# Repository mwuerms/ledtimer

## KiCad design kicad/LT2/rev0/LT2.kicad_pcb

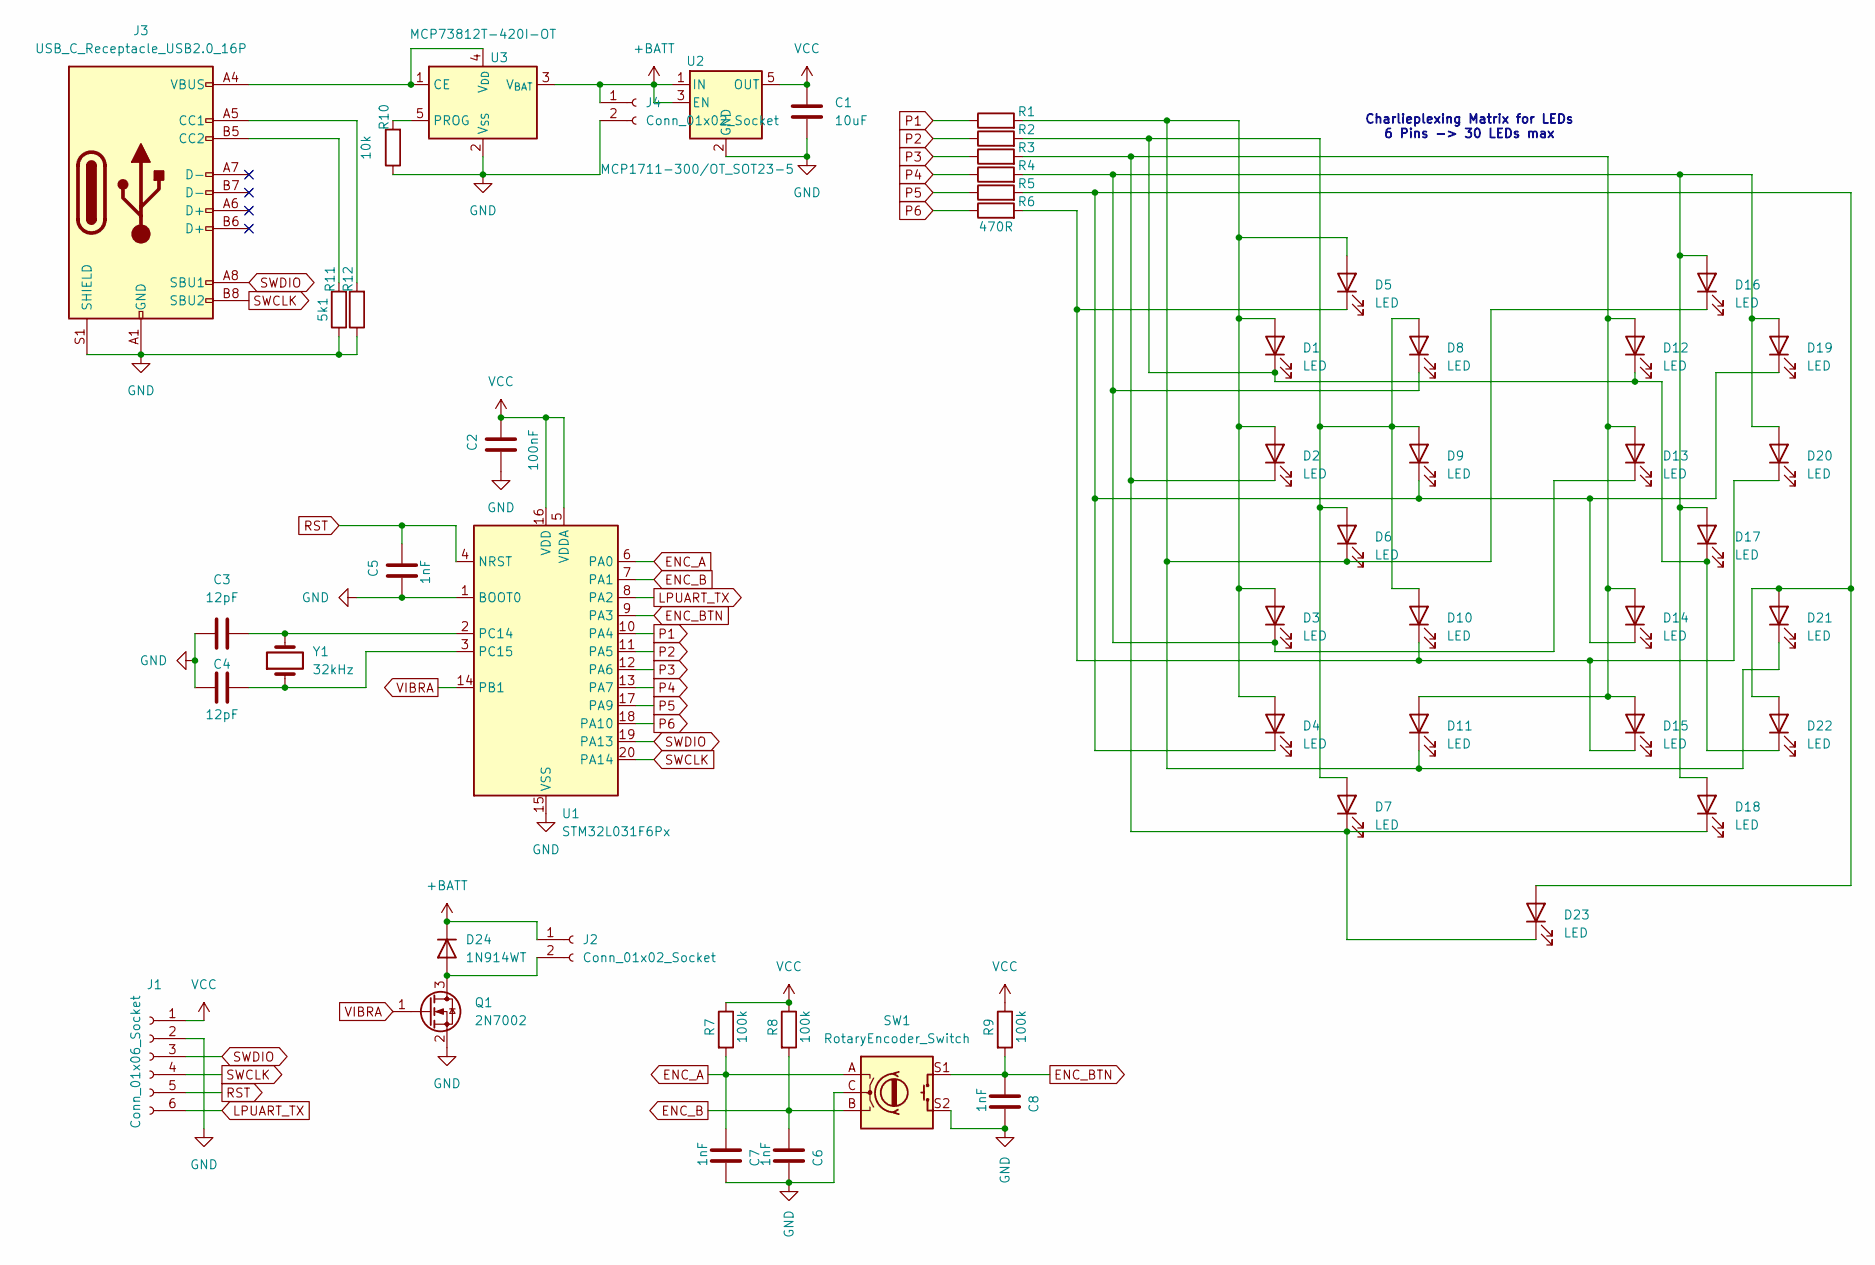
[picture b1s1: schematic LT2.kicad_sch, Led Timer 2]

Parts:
C1: 10uF; C_0805_2012Metric
C2: 100nF; C_0603_1608Metric
C3, C4: 12pF; C_0603_1608Metric
C5, C6, C7, C8: 1nF; C_0603_1608Metric
D1, D2, D3, D4, D5, D6, D7, D8, D9, D10, D11, D12, D13, D14, D15, D16, D17, D18, D19, D20, D21, D22, D23: LED; LED_0603_1608Metric_Pad1.05x0.95mm_HandSolder
D24: 1N914WT; D_SOD-523
J1: Conn_01x06_Socket; PinHeader_1x06_P1.27mm_Vertical
J2, J4: Conn_01x02_Socket; PinHeader_1x02_P1.27mm_Vertical
J3: USB_C_Receptacle_USB2.0_16P; USB_C_Receptacle_G-Switch_GT-USB-7010ASV
Q1: 2N7002; SOT-23
R1, R2, R3, R4, R5, R6: 470R; R_0603_1608Metric
R7, R8, R9: 100k; R_0603_1608Metric
R10: 10k; R_0603_1608Metric
R11, R12: 5k1; R_0603_1608Metric
SW1: RotaryEncoder_Switch; rotary_encoder_PEC11S-929K
U1: STM32L031F6Px; TSSOP-20_4.4x6.5mm_P0.65mm
U2: MCP1711-300/OT_SOT23-5; SOT-23-5
U3: MCP73812T-420I-OT; SOT-23-5
Y1: 32kHz; Crystal_SMD_3215-2Pin_3.2x1.5mm

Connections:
+BATT: D24.1 (K), J2.1, J4.1, U2.1 (IN), U2.3 (EN), U3.3 (V_{BAT})
ENC_A: C7.2, R7.2, SW1.A, U1.6 (PA0)
ENC_B: C6.2, R8.2, SW1.B, U1.7 (PA1)
ENC_BTN: C8.2, R9.2, SW1.S1, U1.9 (PA3)
GND: C1.2, C2.2, C3.1, C4.1, C5.2, C6.1, C7.1, C8.1, J1.2, J3.A1 (GND), J3.A12 (GND), J3.B1 (GND), J3.B12 (GND), J3.S1 (SHIELD), J4.2, Q1.2 (S), R10.1, R11.1, R12.1, SW1.C, SW1.S2, U1.1 (BOOT0), U1.15 (VSS), U2.2 (GND), U3.2 (V_{SS})
LPUART_TX: J1.6, U1.8 (PA2)
unnamed: D1.2 (A), D2.2 (A), D3.2 (A), D4.2 (A), D5.2 (A), D6.1 (K), D11.1 (K), D16.1 (K), D21.1 (K), R1.2
unnamed: D1.1 (K), D6.2 (A), D7.2 (A), D8.2 (A), D9.2 (A), D10.2 (A), D12.1 (K), D17.1 (K), D22.1 (K), R2.2
unnamed: D5.1 (K), D10.1 (K), D15.1 (K), D20.1 (K), R6.2
unnamed: D2.1 (K), D7.1 (K), D11.2 (A), D12.2 (A), D13.2 (A), D14.2 (A), D15.2 (A), D18.1 (K), D23.1 (K), R3.2
unnamed: D3.1 (K), D8.1 (K), D13.1 (K), D16.2 (A), D17.2 (A), D18.2 (A), D19.2 (A), D20.2 (A), R4.2
unnamed: D4.1 (K), D9.1 (K), D14.1 (K), D19.1 (K), D21.2 (A), D22.2 (A), D23.2 (A), R5.2
unnamed: D24.2 (A), J2.2, Q1.3 (D)
unnamed: J3.A5 (CC1), R12.2
unnamed: J3.B5 (CC2), R11.2
unnamed: C3.2, U1.2 (PC14), Y1.2
unnamed: C4.2, U1.3 (PC15), Y1.1
unnamed: J3.A4 (VBUS), J3.A9 (VBUS), J3.B4 (VBUS), J3.B9 (VBUS), U3.1 (CE), U3.4 (V_{DD})
unnamed: R10.2, U3.5 (PROG)
P1: R1.1, U1.10 (PA4)
P2: R2.1, U1.11 (PA5)
P3: R3.1, U1.12 (PA6)
P4: R4.1, U1.13 (PA7)
P5: R5.1, U1.17 (PA9)
P6: R6.1, U1.18 (PA10)
RST: C5.1, J1.5, U1.4 (NRST)
SWCLK: J1.4, J3.B8 (SBU2), U1.20 (PA14)
SWDIO: J1.3, J3.A8 (SBU1), U1.19 (PA13)
VCC: C1.1, C2.1, J1.1, R7.1, R8.1, R9.1, U1.5 (VDDA), U1.16 (VDD), U2.5 (OUT)
VIBRA: Q1.1 (G), U1.14 (PB1)

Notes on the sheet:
Charlieplexing Matrix for LEDs 6 Pins -> 30 LEDs max

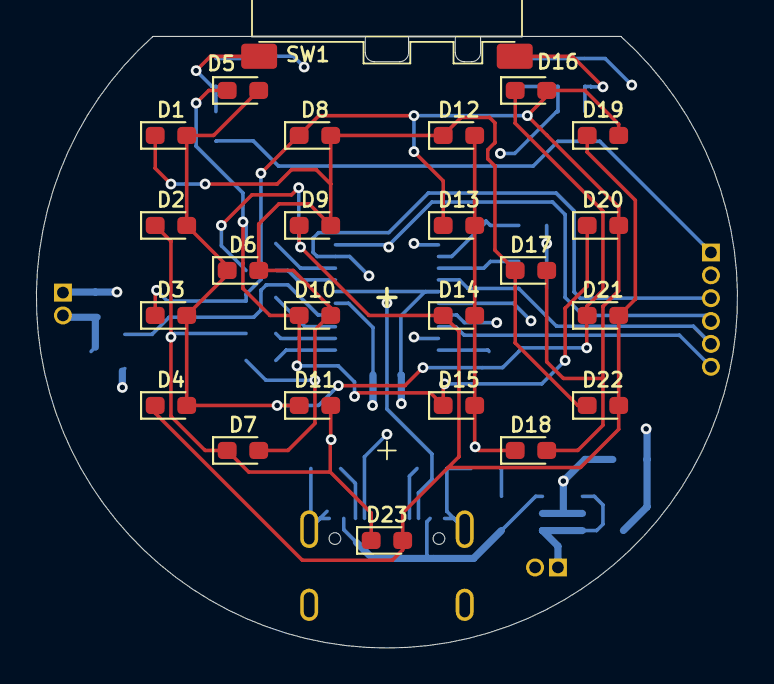
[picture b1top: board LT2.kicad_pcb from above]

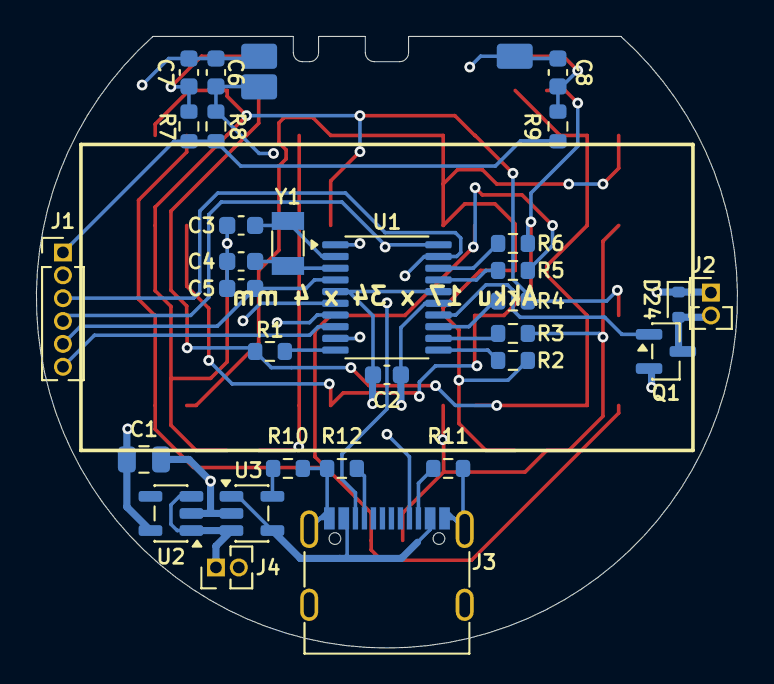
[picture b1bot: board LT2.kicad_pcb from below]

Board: 4 copper layers, 38.9 x 34.0 mm, 54 parts (30 on the bottom side), 30 nets.

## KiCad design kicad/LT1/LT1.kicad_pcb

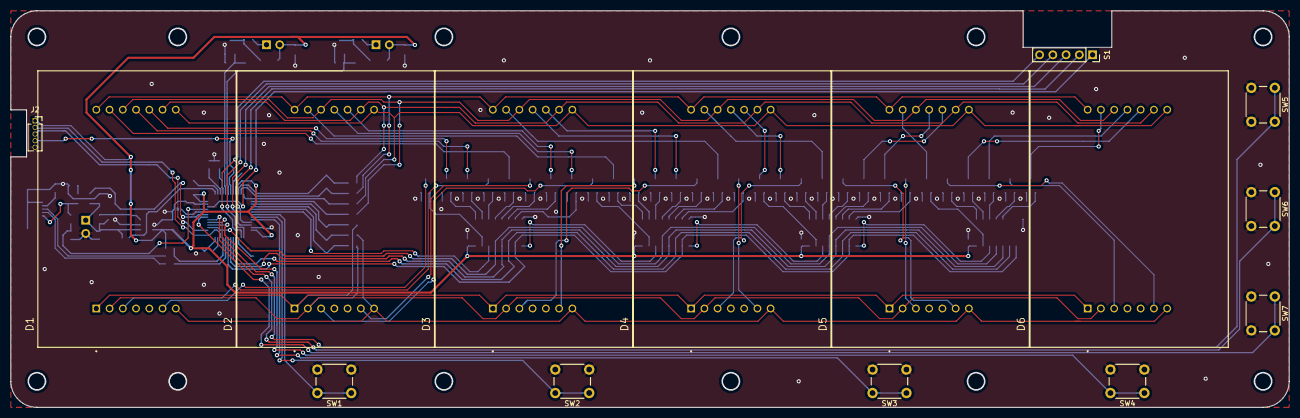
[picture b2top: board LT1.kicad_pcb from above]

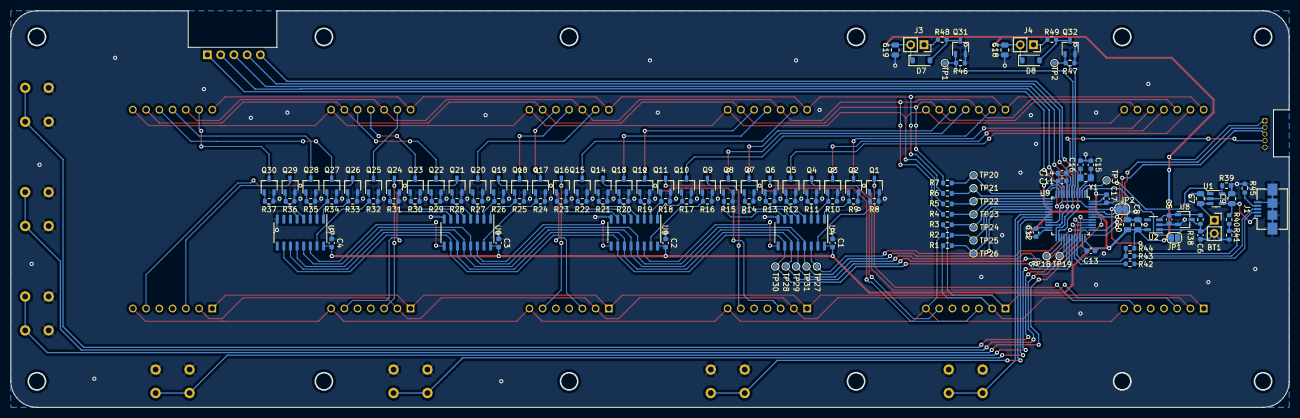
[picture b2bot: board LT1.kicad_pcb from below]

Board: 2 copper layers, 245.0 x 76.0 mm, 149 parts (134 on the bottom side), 123 nets.

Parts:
BT1: Battery_Cell; PinSocket_1x02_P2.54mm_Vertical
C1, C2, C3, C4, C6, C11, C12, C13, C17: 100nF; C_0603_1608Metric
C5, C14: 10nF; C_0603_1608Metric
C7, C8, C9, C10, C18, C19: 10uF; C_0805_2012Metric
C15, C16: C_0603_1608Metric
D1, D2, D3, D4, D5, D6: TC20-11SRWA; LED_TC20-11SRWA
D7, D8: D_Schottky; D_SOD-123
J1: USB_B_Micro; USB_Micro-B_Amphenol_10104110_Horizontal
J2: Conn_01x05_Socket; PinSocket_1x05_P1.27mm_Vertical
J3, J4: Conn_01x02_Socket; PinSocket_1x02_P2.54mm_Vertical
JP1: SolderJumper_2_Open; SolderJumper-2_P1.3mm_Open_RoundedPad1.0x1.5mm
JP2: SolderJumper_2_Bridged; SolderJumper-2_P1.3mm_Bridged_RoundedPad1.0x1.5mm
Q1, Q2, Q3, Q4, Q5, Q6, Q7, Q8, Q9, Q10, Q11, Q12, Q13, Q14, Q15, Q16, Q17, Q18, Q19, Q20, Q21, Q22, Q23, Q24, Q25, Q26, Q27, Q28, Q29, Q30, Q31, Q32: 2N7002K; TSOT-23
R1, R2, R3, R4, R5, R6, R7: 150R; R_0603_1608Metric
R8, R9, R10, R11, R12, R13, R14, R15, R16, R17, R18, R19, R20, R21, R22, R23, R24, R25, R26, R27, R28, R29, R30, R31, R32, R33, R34, R35, R36, R37, R38, R39, R46, R47, R48, R49: 1M; R_0603_1608Metric
R40, R41, R45: 10k; R_0603_1608Metric
R42, R43: 10R; R_0603_1608Metric
R44: 1k5; R_0603_1608Metric
S1: MF140; PinSocket_1x05_P2.54mm_Vertical
SW1, SW2, SW3, SW4, SW5, SW6, SW7: SW_Push; SW_PUSH_6mm_H9.5mm
TP1, TP2, TP3, TP18, TP19, TP20, TP21, TP22, TP23, TP24, TP25, TP26, TP27, TP28, TP29, TP30, TP31: TestPoint; TestPoint_Pad_D1.0mm
U1: MCP73831-2-OT; SOT-23-5
U2: TLV75533PDBV; SOT-23-5
U4, U5, U6, U7: 74HC595D; SO-16_3.9x9.9mm_P1.27mm
U8: MCP111T-xxxE_TT; TSOT-23
U9: STM32L412C8Tx; LQFP-48_7x7mm_P0.5mm
Y1: 32 kHz (ABS06); R_0805_2012Metric_Pad1.20x1.40mm_HandSolder

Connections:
+3.3V: C1.1, C2.1, C3.1, C4.1, C8.1, C10.1, C11.1, C12.1, C13.1, C17.1, C18.1, C19.1, D7.1 (K), D8.1 (K), J2.1, J3.2, J4.2, R44.2, U2.5 (OUT), U4.16 (VCC), U5.16 (VCC), U6.16 (VCC), U7.16 (VCC), U9.9 (VDDA), U9.24 (VDD), U9.36 (VDDUSB), U9.48 (VDD)
+BATT: BT1.1 (+), C6.1, C7.1, JP1.1 (A), R38.1, U1.3 (V_{BAT}), U2.1 (IN), U8.3 (VDD)
ALM0: Q31.1 (G), R46.1, TP1.1, U9.6 (PH1)
ALM1: Q32.1 (G), R47.1, TP2.1, U9.5 (PH0)
BTN_MODE: SW6.1, U9.41 (PB5)
BTN_PLAY: SW5.1, U9.40 (PB4)
BTN_STOP: SW7.1, U9.42 (PB6)
BTN_UP1: SW1.1, U9.18 (PB0)
BTN_UP2: SW2.1, U9.19 (PB1)
BTN_UP3: SW3.1, U9.20 (PB2)
BTN_UP4: SW4.1, U9.39 (PB3)
CH_STAT: U1.1 (STAT), U9.43 (PB7)
DISP_COL_OE: TP31.1, U4.13 (~OE), U5.13 (~OE), U6.13 (~OE), U7.13 (~OE), U9.38 (PA15)
DISP_COL_RCLK: TP29.1, U4.12 (RCLK), U5.12 (RCLK), U6.12 (RCLK), U7.12 (RCLK), U9.30 (PA9)
DISP_COL_SER: TP27.1, U4.14 (SER), U9.17 (PA7)
DISP_COL_SRCLK: TP28.1, U4.11 (SRCLK), U5.11 (SRCLK), U6.11 (SRCLK), U7.11 (SRCLK), U9.29 (PA8)
DISP_COL_SRCLR: TP30.1, U4.10 (~SRCLR), U5.10 (~SRCLR), U6.10 (~SRCLR), U7.10 (~SRCLR), U9.31 (PA10)
DISP_ROW0: R7.1, TP20.1, U9.10 (PA0)
DISP_ROW1: R6.1, TP21.1, U9.11 (PA1)
DISP_ROW2: R5.1, TP22.1, U9.12 (PA2)
DISP_ROW3: R4.1, TP23.1, U9.13 (PA3)
DISP_ROW4: R3.1, TP24.1, U9.14 (PA4)
DISP_ROW5: R2.1, TP25.1, U9.15 (PA5)
DISP_ROW6: R1.1, TP26.1, U9.16 (PA6)
GND: BT1.2 (-), C1.2, C2.2, C3.2, C4.2, C5.2, C6.2, C7.2, C8.2, C9.2, C10.2, C11.2, C12.2, C13.2, C14.2, C15.1, C16.1, C17.2, C18.2, C19.2, J1.5 (GND), J1.6 (Shield), J2.5, JP2.1 (A), Q1.2 (S), Q2.2 (S), Q3.2 (S), Q4.2 (S), Q5.2 (S), Q6.2 (S), Q7.2 (S), Q8.2 (S), Q9.2 (S), Q10.2 (S), Q11.2 (S), Q12.2 (S), Q13.2 (S), Q14.2 (S), Q15.2 (S), Q16.2 (S), Q17.2 (S), Q18.2 (S), Q19.2 (S), Q20.2 (S), Q21.2 (S), Q22.2 (S), Q23.2 (S), Q24.2 (S), Q25.2 (S), Q26.2 (S), Q27.2 (S), Q28.2 (S), Q29.2 (S), Q30.2 (S), Q31.2 (S), Q32.2 (S), R8.2, R9.2, R10.2, R11.2, R12.2, R13.2, R14.2, R15.2, R16.2, R17.2, R18.2, R19.2, R20.2, R21.2, R22.2, R23.2, R24.2, R25.2, R26.2, R27.2, R28.2, R29.2, R30.2, R31.2, R32.2, R33.2, R34.2, R35.2, R36.2, R37.2, R39.2, R41.2, R45.2, R46.2, R47.2, SW1.2, SW2.2, SW3.2, SW4.2, SW5.2, SW6.2, SW7.2, U1.2 (V_{SS}), U2.2 (GND), U4.8 (GND), U5.8 (GND), U6.8 (GND), U7.8 (GND), U8.2 (VSS), U9.8 (VSSA), U9.23 (VSS), U9.35 (VSS), U9.47 (VSS)
unnamed: D1.13 (C1), Q5.3 (D)
unnamed: D1.3 (C2), Q4.3 (D)
unnamed: D1.11 (C3), Q3.3 (D)
unnamed: D1.10 (C4), Q2.3 (D)
unnamed: D1.6 (C5), Q1.3 (D)
unnamed: D1.9 (R1), D2.9 (R1), D3.9 (R1), D4.9 (R1), D5.9 (R1), D6.9 (R1), R7.2
unnamed: D1.14 (R2), D2.14 (R2), D3.14 (R2), D4.14 (R2), D5.14 (R2), D6.14 (R2), R6.2
unnamed: D1.8 (R3), D2.8 (R3), D3.8 (R3), D4.8 (R3), D5.8 (R3), D6.8 (R3), R5.2
unnamed: D1.12 (R4), D2.12 (R4), D3.12 (R4), D4.12 (R4), D5.12 (R4), D6.12 (R4), R4.2
unnamed: D1.1 (R5), D2.1 (R5), D3.1 (R5), D4.1 (R5), D5.1 (R5), D6.1 (R5), R3.2
unnamed: D1.7 (R6), D2.7 (R6), D3.7 (R6), D4.7 (R6), D5.7 (R6), D6.7 (R6), R2.2
unnamed: D1.2 (R7), D2.2 (R7), D3.2 (R7), D4.2 (R7), D5.2 (R7), D6.2 (R7), R1.2
unnamed: D2.13 (C1), Q10.3 (D)
unnamed: D2.3 (C2), Q9.3 (D)
unnamed: D2.11 (C3), Q8.3 (D)
unnamed: D2.10 (C4), Q7.3 (D)
unnamed: D2.6 (C5), Q6.3 (D)
unnamed: D3.13 (C1), Q15.3 (D)
unnamed: D3.3 (C2), Q14.3 (D)
unnamed: D3.11 (C3), Q13.3 (D)
unnamed: D3.10 (C4), Q12.3 (D)
unnamed: D3.6 (C5), Q11.3 (D)
unnamed: D4.13 (C1), Q20.3 (D)
unnamed: D4.3 (C2), Q19.3 (D)
unnamed: D4.11 (C3), Q18.3 (D)
unnamed: D4.10 (C4), Q17.3 (D)
unnamed: D4.6 (C5), Q16.3 (D)
unnamed: D5.13 (C1), Q25.3 (D)
unnamed: D5.3 (C2), Q24.3 (D)
unnamed: D5.11 (C3), Q23.3 (D)
unnamed: D5.10 (C4), Q22.3 (D)
unnamed: D5.6 (C5), Q21.3 (D)
unnamed: D6.13 (C1), Q30.3 (D)
unnamed: D6.3 (C2), Q29.3 (D)
unnamed: D6.11 (C3), Q28.3 (D)
unnamed: D6.10 (C4), Q27.3 (D)
unnamed: D6.6 (C5), Q26.3 (D)
unnamed: D7.2 (A), Q31.3 (D), R48.2
unnamed: D8.2 (A), Q32.3 (D), R49.2
unnamed: J1.4 (ID), R45.1
unnamed: J3.1, R48.1
unnamed: J4.1, R49.1
unnamed: JP1.2 (B), U9.1 (VBAT)
unnamed: JP2.2 (B), U9.44 (PH3)
unnamed: Q1.1 (G), R8.1, U4.15 (QA)
unnamed: Q2.1 (G), R9.1, U4.1 (QB)
unnamed: Q3.1 (G), R10.1, U4.2 (QC)
unnamed: Q4.1 (G), R11.1, U4.3 (QD)
unnamed: Q5.1 (G), R12.1, U4.4 (QE)
unnamed: Q6.1 (G), R13.1, U4.5 (QF)
unnamed: Q7.1 (G), R14.1, U4.6 (QG)
unnamed: Q8.1 (G), R15.1, U4.7 (QH)
unnamed: Q9.1 (G), R16.1, U5.15 (QA)
unnamed: Q10.1 (G), R17.1, U5.1 (QB)
unnamed: Q11.1 (G), R18.1, U5.2 (QC)
unnamed: Q12.1 (G), R19.1, U5.3 (QD)
unnamed: Q13.1 (G), R20.1, U5.4 (QE)
unnamed: Q14.1 (G), R21.1, U5.5 (QF)
unnamed: Q15.1 (G), R22.1, U5.6 (QG)
unnamed: Q16.1 (G), R23.1, U5.7 (QH)
unnamed: Q17.1 (G), R24.1, U6.15 (QA)
unnamed: Q18.1 (G), R25.1, U6.1 (QB)
unnamed: Q19.1 (G), R26.1, U6.2 (QC)
unnamed: Q20.1 (G), R27.1, U6.3 (QD)
unnamed: Q21.1 (G), R28.1, U6.4 (QE)
unnamed: Q22.1 (G), R29.1, U6.5 (QF)
unnamed: Q23.1 (G), R30.1, U6.6 (QG)
unnamed: Q24.1 (G), R31.1, U6.7 (QH)
unnamed: Q25.1 (G), R32.1, U7.15 (QA)
unnamed: Q26.1 (G), R33.1, U7.1 (QB)
unnamed: Q27.1 (G), R34.1, U7.2 (QC)
unnamed: Q28.1 (G), R35.1, U7.3 (QD)
unnamed: Q29.1 (G), R36.1, U7.4 (QE)
unnamed: Q30.1 (G), R37.1, U7.5 (QF)
unnamed: R39.1, U1.5 (PROG)
unnamed: C5.1, R38.2, U2.3 (EN), U8.1 (VOUT)
unnamed: U4.9 (QH'), U5.14 (SER)
unnamed: U5.9 (QH'), U6.14 (SER)
unnamed: U6.9 (QH'), U7.14 (SER)
unnamed: R42.1, U9.32 (PA11)
unnamed: R43.1, R44.1, U9.33 (PA12)
unnamed: TP18.1, U9.27 (PB14)
unnamed: TP19.1, U9.28 (PB15)
unnamed: TP3.1, U9.2 (PC13)
unnamed: C15.2, U9.3 (PC14), Y1.2
unnamed: C16.2, U9.4 (PC15), Y1.1
SW0: S1.1, U9.46 (PB9)
SW1: S1.2, U9.21 (PB10)
SW2: S1.3, U9.22 (PB11)
SW3: S1.4, U9.25 (PB12)
SW4: S1.5, U9.26 (PB13)
SWDCLK: J2.3, U9.37 (PA14)
SWDIO: J2.2, U9.34 (PA13)
USBD+: J1.3 (D+), R43.2
USBD-: J1.2 (D-), R42.2
USB_STAT: R40.2, R41.1, U9.45 (PB8)
VBUS: C9.1, J1.1 (VBUS), R40.1, U1.4 (V_{DD})
nRST: C14.1, J2.4, U9.7 (NRST)

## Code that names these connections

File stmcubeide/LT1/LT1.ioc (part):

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Mcu.Name=STM32L412CBTx
Mcu.Package=LQFP48
Mcu.UserName=STM32L412CBTx
PA0.GPIOParameters=GPIO_Speed,GPIO_Label
PA0.GPIO_Label=DISP_ROW0
PA0.GPIO_Speed=GPIO_SPEED_FREQ_HIGH
PA0.Signal=GPIO_Output
PA1.GPIOParameters=GPIO_Speed,GPIO_Label
PA1.GPIO_Label=DISP_ROW1
PA1.GPIO_Speed=GPIO_SPEED_FREQ_HIGH
PA1.Signal=GPIO_Output
PA10.GPIOParameters=GPIO_Speed,GPIO_Label
PA10.GPIO_Label=DISP_COL_SRCLR
PA10.GPIO_Speed=GPIO_SPEED_FREQ_HIGH
PA10.Signal=GPIO_Output
PA13\ (JTMS/SWDIO).Mode=Serial_Wire
PA13\ (JTMS/SWDIO).Signal=SYS_JTMS-SWDIO
PA14\ (JTCK/SWCLK).Mode=Serial_Wire
PA14\ (JTCK/SWCLK).Signal=SYS_JTCK-SWCLK
PA15\ (JTDI).GPIOParameters=GPIO_Speed,GPIO_Label
PA15\ (JTDI).GPIO_Label=DISP_COL_OE
PA15\ (JTDI).GPIO_Speed=GPIO_SPEED_FREQ_HIGH
PA15\ (JTDI).Signal=GPIO_Output
PA2.GPIOParameters=GPIO_Speed,GPIO_Label
PA2.GPIO_Label=DISP_ROW2
PA2.GPIO_Speed=GPIO_SPEED_FREQ_HIGH
PA2.Signal=GPIO_Output
PA3.GPIOParameters=GPIO_Speed,GPIO_Label
PA3.GPIO_Label=DISP_ROW3
PA3.GPIO_Speed=GPIO_SPEED_FREQ_HIGH
PA3.Signal=GPIO_Output
PA4.GPIOParameters=GPIO_Speed,GPIO_Label
PA4.GPIO_Label=DISP_ROW4
PA4.GPIO_Speed=GPIO_SPEED_FREQ_HIGH
PA4.Signal=GPIO_Output
PA5.GPIOParameters=GPIO_Speed,GPIO_Label
PA5.GPIO_Label=DISP_ROW5
PA5.GPIO_Speed=GPIO_SPEED_FREQ_HIGH
PA5.Signal=GPIO_Output
PA6.GPIOParameters=GPIO_Speed,GPIO_Label
PA6.GPIO_Label=DISP_ROW6
PA6.GPIO_Speed=GPIO_SPEED_FREQ_HIGH
PA6.Signal=GPIO_Output
PA7.GPIOParameters=GPIO_Speed,GPIO_Label
PA7.GPIO_Label=DISP_COL_SER
PA7.GPIO_Speed=GPIO_SPEED_FREQ_HIGH
PA7.Signal=GPIO_Output
PA8.GPIOParameters=GPIO_Speed,GPIO_Label
PA8.GPIO_Label=DISP_COL_SRCLK
PA8.GPIO_Speed=GPIO_SPEED_FREQ_HIGH
PA8.Signal=GPIO_Output
PA9.GPIOParameters=GPIO_Speed,GPIO_Label
PA9.GPIO_Label=DISP_COL_RCLK
PA9.GPIO_Speed=GPIO_SPEED_FREQ_HIGH
PA9.Signal=GPIO_Output
PB0.GPIOParameters=GPIO_PuPd,GPIO_Label
PB0.GPIO_Label=BTN_UP0
PB0.GPIO_PuPd=GPIO_PULLUP
PB0.Signal=GPXTI0
PB1.GPIOParameters=GPIO_PuPd,GPIO_Label
PB1.GPIO_Label=BTN_UP1
PB1.GPIO_PuPd=GPIO_PULLUP
PB1.Signal=GPXTI1
PB10.GPIOParameters=GPIO_PuPd,GPIO_Label
PB10.GPIO_Label=SW1
PB10.GPIO_PuPd=GPIO_PULLDOWN
PB10.Signal=GPIO_Input
PB11.GPIOParameters=GPIO_PuPd,GPIO_Label
PB11.GPIO_Label=SW2
PB11.GPIO_PuPd=GPIO_PULLDOWN
PB11.Signal=GPIO_Input
PB12.GPIOParameters=GPIO_PuPd,GPIO_Label
PB12.GPIO_Label=SW3
PB12.GPIO_PuPd=GPIO_PULLDOWN
PB12.Signal=GPIO_Input
PB13.GPIOParameters=GPIO_PuPd,GPIO_Label
PB13.GPIO_Label=SW4
PB13.GPIO_PuPd=GPIO_PULLDOWN
PB13.Signal=GPIO_Input
PB2.GPIOParameters=GPIO_PuPd,GPIO_Label
PB2.GPIO_Label=BTN_UP2
PB2.GPIO_PuPd=GPIO_PULLUP
PB2.Signal=GPXTI2
PB3\ (JTDO/TRACESWO).GPIOParameters=GPIO_PuPd,GPIO_Label
PB3\ (JTDO/TRACESWO).GPIO_Label=BTN_UP3
PB3\ (JTDO/TRACESWO).GPIO_PuPd=GPIO_PULLUP
PB3\ (JTDO/TRACESWO).Signal=GPXTI3
PB4\ (NJTRST).GPIOParameters=GPIO_PuPd,GPIO_Label
PB4\ (NJTRST).GPIO_Label=BTN_PLAY
PB4\ (NJTRST).GPIO_PuPd=GPIO_PULLUP
PB4\ (NJTRST).Signal=GPXTI4
PB5.GPIOParameters=GPIO_PuPd,GPIO_Label
PB5.GPIO_Label=BTN_MODE
PB5.GPIO_PuPd=GPIO_PULLUP
PB5.Signal=GPXTI5
PB6.GPIOParameters=GPIO_PuPd,GPIO_Label
PB6.GPIO_Label=BTN_STOP
PB6.GPIO_PuPd=GPIO_PULLUP
PB6.Signal=GPXTI6
PB7.GPIOParameters=GPIO_Label
PB7.GPIO_Label=CH_STAT
PB7.Signal=GPIO_Input
PB8.GPIOParameters=GPIO_Label
PB8.GPIO_Label=USB_STAT
PB8.Signal=GPXTI8
PB9.GPIOParameters=GPIO_PuPd,GPIO_Label
PB9.GPIO_Label=SW0
PB9.GPIO_PuPd=GPIO_PULLDOWN
PB9.Signal=GPIO_Input
PC13.GPIOParameters=GPIO_Label
PC13.GPIO_Label=USR_BTN
PC13.Signal=GPXTI13
PH0-OSC_IN\ (PH0).GPIOParameters=GPIO_Label
PH0-OSC_IN\ (PH0).GPIO_Label=ALM0
PH0-OSC_IN\ (PH0).Signal=GPIO_Output
PH1-OSC_OUT\ (PH1).GPIOParameters=GPIO_Label
PH1-OSC_OUT\ (PH1).GPIO_Label=ALM1
PH1-OSC_OUT\ (PH1).Signal=GPIO_Output
RCC.HSE_VALUE=8000000
RCC.SYSCLKFreq_VALUE=16000000
RCC.SYSCLKSource=RCC_SYSCLKSOURCE_HSI
board=custom

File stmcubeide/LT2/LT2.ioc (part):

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Mcu.Name=STM32L031F(4-6)Px
Mcu.Package=TSSOP20
Mcu.UserName=STM32L031F6Px
PA0-CK_IN.GPIOParameters=GPIO_Label,GPIO_ModeDefaultEXTI
PA0-CK_IN.GPIO_Label=ENC_A
PA0-CK_IN.GPIO_ModeDefaultEXTI=GPIO_MODE_IT_RISING_FALLING
PA0-CK_IN.Signal=GPXTI0
PA1.GPIOParameters=GPIO_Label
PA1.GPIO_Label=ENC_B
PA1.Signal=GPIO_Input
PA10.GPIOParameters=GPIO_Label
PA10.GPIO_Label=P6
PA10.Signal=GPIO_Output
PA13.Mode=Serial_Wire
PA13.Signal=SYS_SWDIO
PA14.Mode=Serial_Wire
PA14.Signal=SYS_SWCLK
PA2.Signal=GPIO_Output
PA3.GPIOParameters=GPIO_Label,GPIO_ModeDefaultEXTI
PA3.GPIO_Label=ENC_BTN
PA3.GPIO_ModeDefaultEXTI=GPIO_MODE_IT_RISING_FALLING
PA3.Signal=GPXTI3
PA4.GPIOParameters=GPIO_Label
PA4.GPIO_Label=P1
PA4.Signal=GPIO_Output
PA5.GPIOParameters=GPIO_Label
PA5.GPIO_Label=P2
PA5.Signal=GPIO_Output
PA6.GPIOParameters=GPIO_Label
PA6.GPIO_Label=P3
PA6.Signal=GPIO_Output
PA7.GPIOParameters=GPIO_Label
PA7.GPIO_Label=P4
PA7.Signal=GPIO_Output
PA9.GPIOParameters=GPIO_Label
PA9.GPIO_Label=P5
PA9.Signal=GPIO_Output
PB1.GPIOParameters=GPIO_Label
PB1.GPIO_Label=VIBRA
PB1.Signal=GPIO_Output
PC14-OSC32_IN.Mode=LSE-External-Oscillator
PC14-OSC32_IN.Signal=RCC_OSC32_IN
PC15-OSC32_OUT.Mode=LSE-External-Oscillator
PC15-OSC32_OUT.Signal=RCC_OSC32_OUT
RCC.HSE_VALUE=8000000
RCC.SYSCLKFreq_VALUE=16000000
RCC.SYSCLKSource=RCC_SYSCLKSOURCE_HSI
board=custom

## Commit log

2023-09-13 added some images, fonts and some openscad
2023-09-16 openscad: some changes to front plate kicad: started with schematics
2023-09-20 schematics: added led matrix display, did much on MCU
2023-09-20 LT1 schema done
2023-09-23 LT1 started with PCB, added driver for piezo and vibra alarm
2023-09-24 LT1 some routing and placing
2023-09-27 LT1 all routed, gerber exported
2023-09-27 LT1: new stm32cubeide project created
2023-09-28 LT1: added event loop (not done yet, but it works) lptim added events display added 1 segment
2023-09-28 LT1: changed LT1.ioc to get EXTI (interrupts on gpios)
2023-09-30 LT1: addeded display_ShowBuffer gpio: reading buttons works, getting correct states
2023-10-01 LT1: added apps
2023-10-16 LT1: split display into dispBuffer and display
2023-10-16 dispBuffer: moved disp_buffer operation routines here
2023-10-17 LT1: using mainapp/timer1app_ProcessEvents()
2023-10-18 LT1: BOM + PDF exported
2023-10-18 LT1 timer1app set time
2023-12-13 LT1: Buttons working Display working but had to do 2 bugfixes: LED display was 180° rotated, but still flickering, need to adjust timing
2023-12-21 LT1: fixed timing, now display and gpios work both from foreground gpios tested, added func to detect button change
2023-12-21 LT1: using lptim1 for display
2023-12-21 LT1: timer1app setting time done
2023-12-26 LT1: added timer45minapp, there will be 1 single uninterruptable 45 min timing countdown
2024-01-02 LT1: new folder
2024-01-02 LT1: added pcb with components
2025-10-08 started LED Timer 2
2025-10-18 placing battey + rot encoder
2025-10-18 some routing
2025-10-19 LT2 rev0 done, ordered
2025-10-22 started stm32 LT2
2025-10-22 scheduler added
2025-10-22 started with encoder + display
2025-10-22 disp, charlieplexing driver
2025-10-22 more disp
2025-10-27 added EV_ENC_SINGLE_PRESSED, _DOUBLE_PRESSED, LONG_PRESSED
2025-10-29 testing 1
    encoder left/right works,
    encoder btn single, double and long pressed works, but timing is still a
    bit long
    but display (charlieplexing) does not work propperly, although
    somethings work
2025-10-29 disp works fine now
2025-10-29 added more timers, rtc WUT works
2025-10-29 timing tested: 1 s is really 1 s, also casing -> openscad
2025-10-30 rtc functions
2025-10-30 case v1.1
2025-11-01 main_task structure and events, encoder use TIM21
2025-11-01 main_task basic funct seems to work
2025-11-12 added sleep + stop mode, works
2025-11-23 added sleep modes and alarm inactive timeout
2025-11-23 case minor adjustments for vibra motor
2025-12-07 vibra quickly implemented: works
